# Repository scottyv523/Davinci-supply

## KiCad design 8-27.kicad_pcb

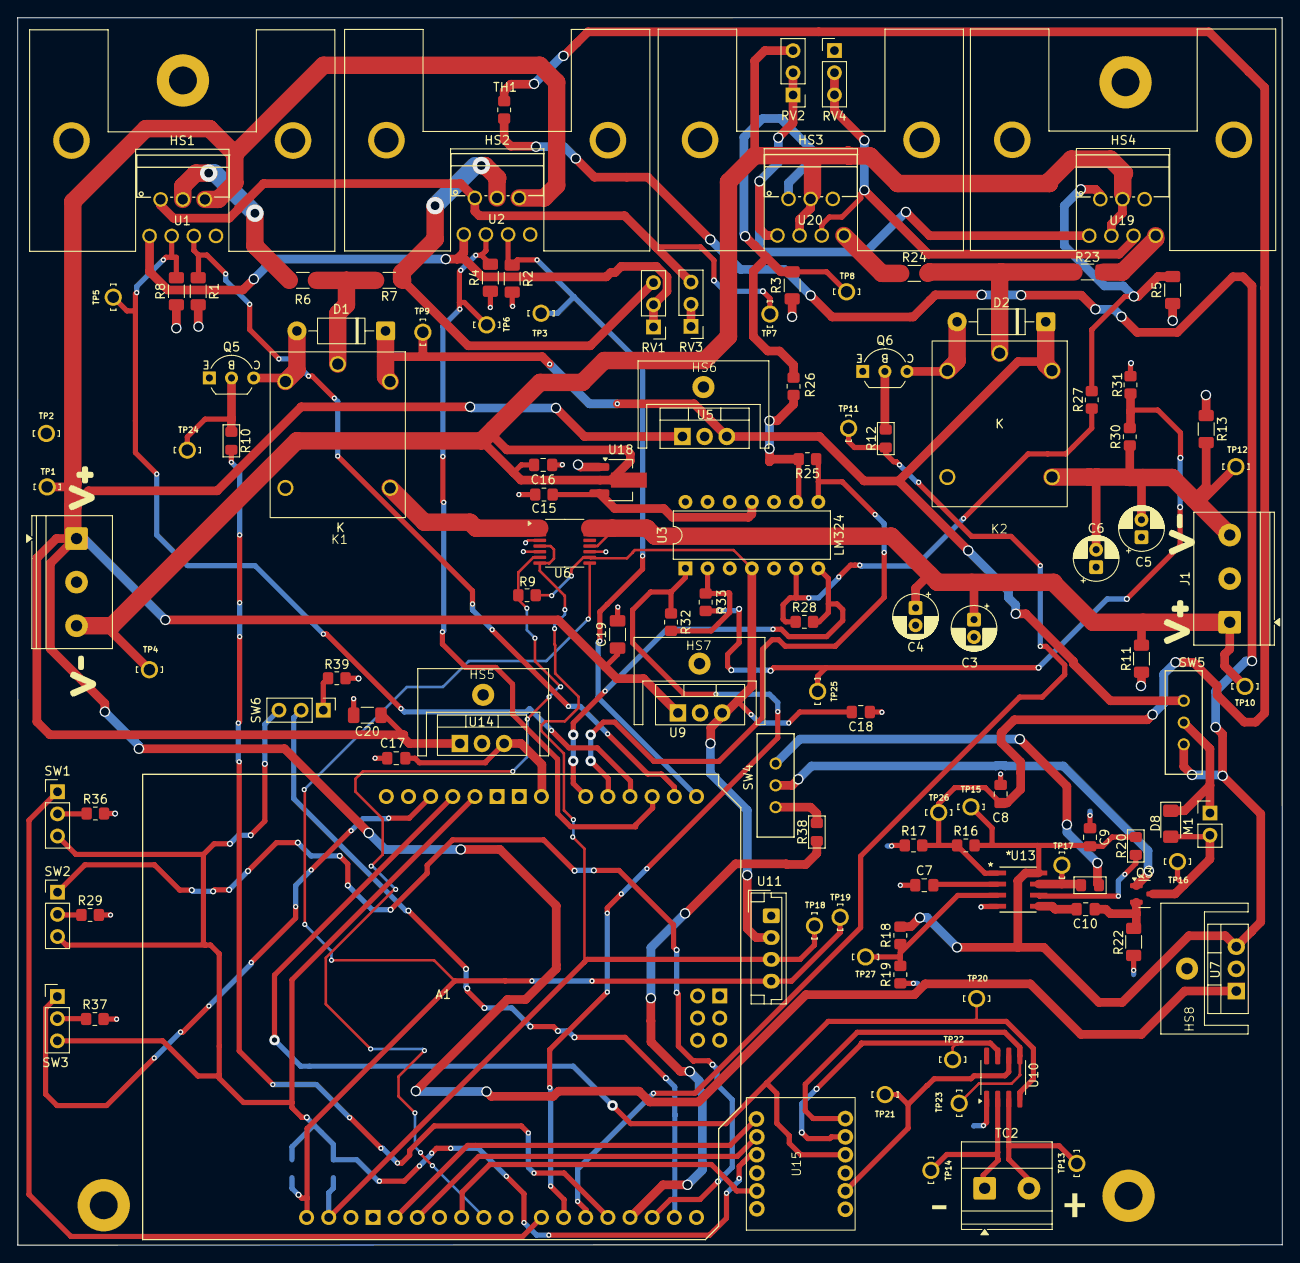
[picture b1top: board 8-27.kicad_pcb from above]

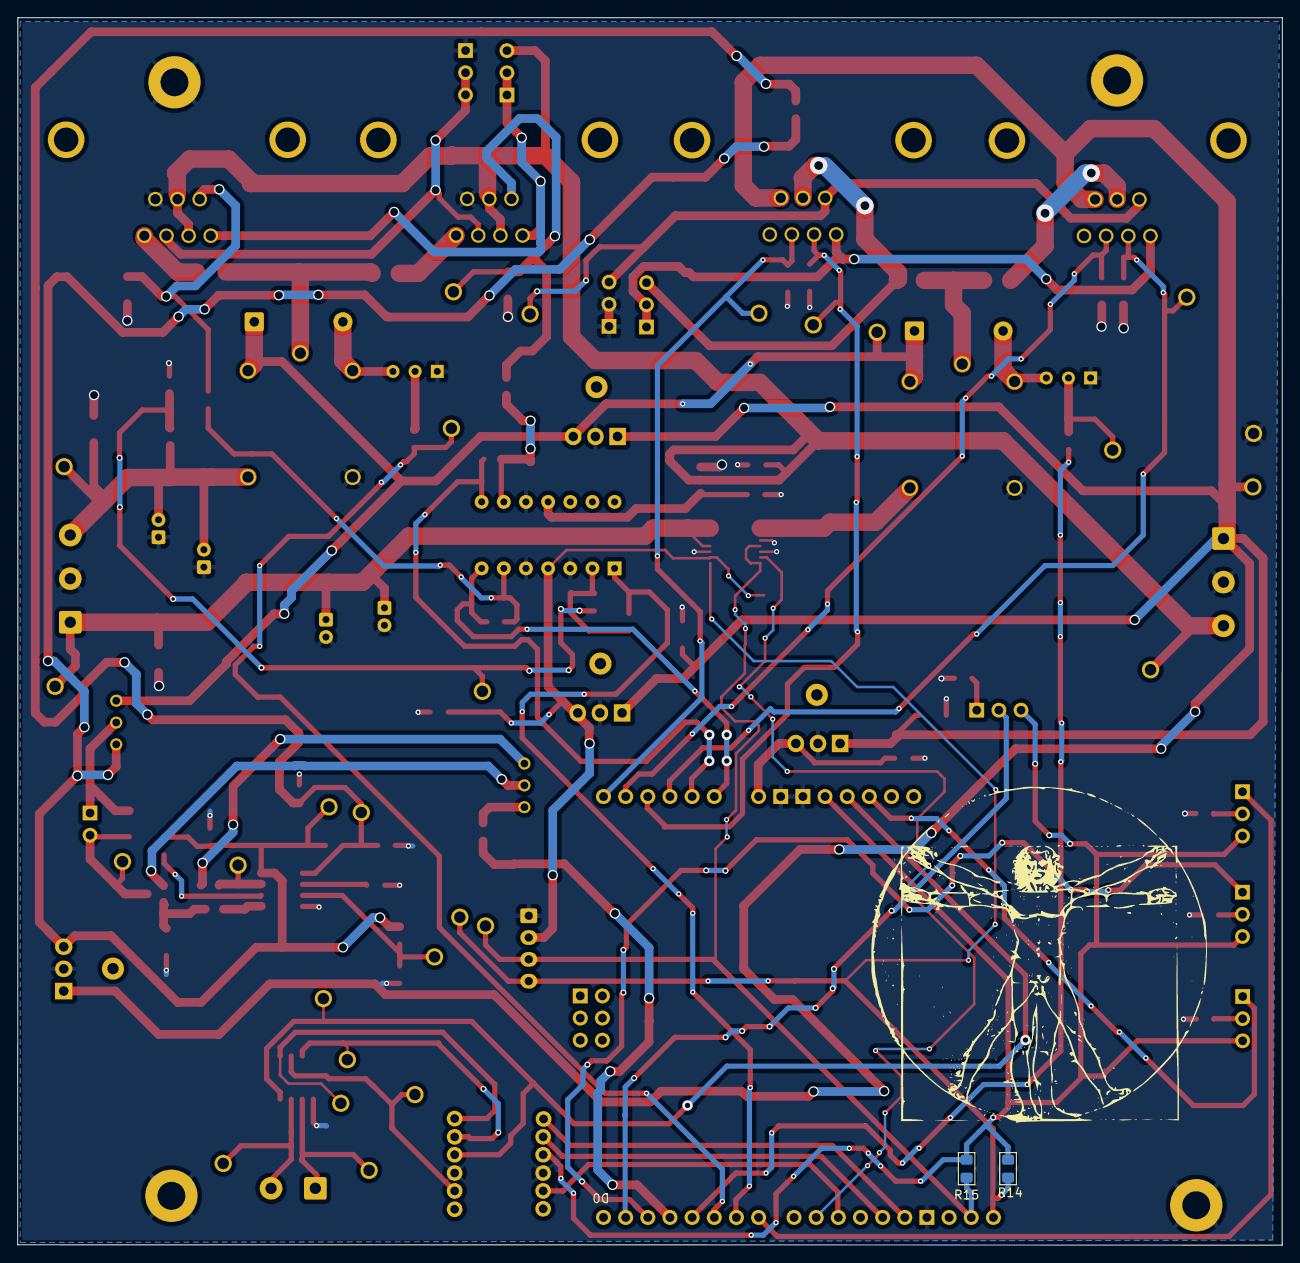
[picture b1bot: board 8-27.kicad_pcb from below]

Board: 2 copper layers, 145.0 x 140.7 mm, 135 parts (7 on the bottom side), 74 nets.

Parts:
A1: Arduino_Leonardo
C3, C4, C5, C6: 10uF; CP_Radial_D5.0mm_P2.00mm
C7, C9: 1uF; C_0805_2012Metric_Pad1.18x1.45mm_HandSolder
C8: .01uF; C_0805_2012Metric_Pad1.18x1.45mm_HandSolder
C10: .1uF; C_0805_2012Metric_Pad1.18x1.45mm_HandSolder
C15: .1uF; R_0805_2012Metric_Pad1.20x1.40mm_HandSolder
C16: .33uF; C_0805_2012Metric_Pad1.18x1.45mm_HandSolder
C17, C18: 1 uF; C_0805_2012Metric_Pad1.18x1.45mm_HandSolder
C19, C20: 33 uF; C_1206_3216Metric_Pad1.33x1.80mm_HandSolder
D1, D2: 1N4007; D_DO-41_SOD81_P10.16mm_Horizontal
D8: D_Schottky_Generic; D_1206_3216Metric_Pad1.42x1.75mm_HandSolder
H1, H2, H3, H4: M3_Hole_With_Spacer_H10mm; MountingHole_3.2mm_With_Spacer_H10mm
HS1, HS2, HS3, HS4: HSE-B250-04H; HSINK_HSE-B250-04H
HS5, HS6, HS7, HS8: Heatsink; Heatsink Amazon
J1: Power Out; TerminalBlock_Phoenix_PT-1,5-3-5.0-H_1x03_P5.00mm_Horizontal
J2: Power In; TerminalBlock_Phoenix_PT-1,5-3-5.0-H_1x03_P5.00mm_Horizontal
K1, K2: Relay_SPDT; JQC-3F(T73)
M1: Fan; PinHeader_1x02_P2.54mm_Vertical
Q3: MMBT2222A; SOT-23
Q5, Q6: 2N2222A-TO92; TO-92_Inline_Wide_EBC
R1, R2: 5k; R_1206_3216Metric_Pad1.30x1.75mm_HandSolder
R3, R4, R5, R8, R11, R13: 10K; R_1206_3216Metric_Pad1.30x1.75mm_HandSolder
R6, R7, R23, R24: 10m; R_1206_3216Metric_Pad1.30x1.75mm_HandSolder
R9: 2K2; R_0805_2012Metric_Pad1.20x1.40mm_HandSolder
R10, R12: 1K; R_0805_2012Metric_Pad1.15x1.40mm_HandSolder
R14, R15, R20: 10K; R_0805_2012Metric_Pad1.15x1.40mm_HandSolder
R16: 237K; R_0805_2012Metric_Pad1.20x1.40mm_HandSolder
R17: 45.3K; R_0805_2012Metric_Pad1.20x1.40mm_HandSolder
R18: 32.4K; R_0805_2012Metric_Pad1.20x1.40mm_HandSolder
R19: 17.8K; R_0805_2012Metric_Pad1.20x1.40mm_HandSolder
R21, R38: 800; R_0805_2012Metric_Pad1.15x1.40mm_HandSolder
R22: 3; R_1206_3216Metric_Pad1.30x1.75mm_HandSolder
R25, R28, R29, R31, R36, R37, R39: 10K; R_0805_2012Metric_Pad1.20x1.40mm_HandSolder
R26, R27: 0R; R_0805_2012Metric_Pad1.20x1.40mm_HandSolder
R30: 50K; R_0805_2012Metric_Pad1.20x1.40mm_HandSolder
R32, R33: 100K; R_0805_2012Metric_Pad1.20x1.40mm_HandSolder
RV1: 200K; PinHeader_1x03_P2.54mm_Vertical
RV2: 50K; PinHeader_1x03_P2.54mm_Vertical
RV3, RV4: 500K; PinHeader_1x03_P2.54mm_Vertical
SW1, SW2, SW3, SW6: SW_MEC_5E; PinHeader_1x03_P2.54mm_Vertical
SW4, SW5: SW_SPDT; SW_1218_SPDT
TC2: Thermocouple_Block; TerminalBlock_Phoenix_MKDS-1,5-2-5.08_1x02_P5.08mm_Horizont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
TH1: Thermistor; R_0805_2012Metric_Pad1.20x1.40mm_HandSolder
TP1, TP2, TP3, TP4, TP5, TP6, TP7, TP8, TP9, TP10, TP11, TP12, TP13, TP14, TP15, TP16, TP17, TP18, TP19, TP20, TP21, TP22, TP23, TP24, TP25, TP26, TP27: TestPoint; KEYSTONE_4952
U1, U2: LT3081xT7; TO220-7_T_LIT
U3: LM324; DIP-14_W7.62mm
U5: LM7812_TO220; TO-220-3_Vertical
U6: INA260; TSSOP-16_4.4x5mm_P0.65mm
U7: LM7805CT; TO-220-3_Vertical
U9: LM7805_TO220; TO-220-3_Vertical
U10: MAX31855KASA; SOIC-8_3.9x4.9mm_P1.27mm
U11: LCD 20x04; JST_EH_B4B-EH-A_1x04_P2.50mm_Vertical
U13: TC647BEOATR; SOIC8-N_MC_MCH
U14: L7808CV; TO-220-3_Vertical
U15: Hiletgo I2C LLC Bi-Directional 3.3-5V; Hiletgo LLC
U18: L7905; SOT-89-3_Handsoldering
U19, U20: LT3091ET7-PBF; TO220-7_T_LIT
kibuzzard-68CB74DE: G***; kibuzzard-68CB74DE
kibuzzard-68CB74F5: G***; kibuzzard-68CB74F5
kibuzzard-68CB749D: G***; kibuzzard-68CB749D
kibuzzard-68CB751C: G***; kibuzzard-68CB751C
kibuzzard-68CB7484: G***; kibuzzard-68CB7484
kibuzzard-68CB7542: G***; kibuzzard-68CB7542

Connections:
+12V: D1.1 (K), D2.1 (K), K1.2 (in), K2.2 (in), SW5.3 (C), TP9.1, U5.3 (VO)
/CLK: A1.28 (D13), U15.7 (HV1)
/Chip Select: A1.25 (D10), U15.11 (HV3)
/Control PCB/3V3: A1.4 (3V3), TP20.1, U10.4 (V_{CC}), U15.3 (LV)
/Control PCB/+5V: C18.2, R9.1, U3.4 (V+), U6.10 (VS), U9.3 (VO), U11.2 (VCC)
/Control PCB/+5V ARD VS: A1.5 (+5V), R14.2, R15.2, SW1.3 (K), SW2.3 (K), SW3.3 (K), SW6.3 (K), U15.9 (HV)
/Control PCB/- Vsense: A1.21 (D6), R32.1, U3.1
/Control PCB/A0 port: A1.9 (A0), R28.2, U3.7
/Control PCB/A1 port: A1.10 (A1), R25.1, U3.8
/Control PCB/A2 port: A1.11 (A2), R8.2, TP5.1, U1.3 (IMON)
/Control PCB/A3 port: A1.12 (A3), R4.2, TP6.1, U2.3 (IMON)
/Control PCB/ARD SCL: A1.32 (SCL/D3), R14.1, TP19.1, U6.9 (SCL), U11.4 (SCL)
/Control PCB/ARD SDA: A1.31 (SDA/D2), R15.1, TP18.1, U6.5 (A0), U6.8 (SDA), U11.3 (SDA)
/Control PCB/D3 PWM: A1.18 (D3/SCL), R38.1
/Control PCB/D4 I/O: A1.19 (D4), R10.2
/Control PCB/D5 I/O: A1.20 (D5), R12.1, TP11.1
/Control PCB/INA Alert: A1.24 (D9), R9.2, U6.7 (ALERT)
/Data: A1.27 (D12), U15.8 (HV2)
/LT3081_3091 REGULATOR PCB/-V ADJ Out: C5.2, C6.2, J1.3, K2.4 (NC), R13.2, R30.2, TP12.1
/LT3081_3091 REGULATOR PCB/I LIM/ADJ: RV1.1, RV1.2, U1.1 (ILIM), U2.1 (ILIM)
/LT3081_3091 REGULATOR PCB/Temp 1: A1.13 (A4), R1.1, U1.5 (TEMP)
/LT3081_3091 REGULATOR PCB/Temp 2: A1.14 (A5), R2.1, TP3.1, U2.5 (TEMP)
/LT3081_3091 REGULATOR PCB/V Set: RV3.3, TP7.1, U1.2 (SET), U2.2 (SET)
/LT3081_3091 REGULATOR PCB/V+ ADJ Out: C3.1, C4.1, J1.1, R11.1, TP10.1, U6.12 (VBUS), U6.14 (IN-), U6.15 (IN-), U6.16 (IN-)
/LT3081_3091 REGULATOR PCB/V+ PRE-REG: C19.1, C20.1, J2.1, TP1.1, U1.6 (IN), U2.6 (IN), U5.1 (VI), U7.1 (IN), U9.1 (VI), U14.1 (IN)
/LT3081_3091 REGULATOR PCB/V- ADJ Out: K2.1 (COM), R23.2, R24.2
/LT3081_3091 REGULATOR PCB/V- PRE-REG: C16.2 (-), J2.3, RV2.3, TP4.1, U18.2 (VI), U19.3 (*SHDN), U19.4 (IN), U20.3 (*SHDN), U20.4 (IN)
GND: A1.6 (GND), A1.7 (GND), A1.29 (GND), C3.2, C4.2, C5.1, C6.1, C7.1, C8.2, C9.1, C15.1 (+), C16.1 (+), C17.1, C18.1, C19.2, C20.2, H1.1, H2.1, H3.1, H4.1, J1.2, J2.2, K1.5 (NO), K2.5 (NO), Q5.1 (E), Q6.1 (E), R1.2, R2.2, R3.1, R4.1, R5.1, R8.1, R11.2, R13.1, R17.1, R19.1, R22.2, R29.2, R31.1, R36.2, R37.2, R39.1, RV3.1, RV3.2, RV4.1, TP2.1, U3.3 (+), U3.5 (+), U3.10 (+), U5.2 (GND), U6.4 (A1), U6.6 (GND), U6.11 (GND), U7.2, U9.2 (GND), U10.1 (GND), U11.1 (GND), U13.4 (GND), U14.2, U15.4 (GND), U15.10 (GND), U18.1 (GND), U19.6 (GND), U20.6 (GND)
unnamed: A1.16 (D1/TX), SW6.2
unnamed: A1.17 (D2/SDA), SW2.1
unnamed: A1.22 (D7), SW1.1
unnamed: A1.8 (VIN), C17.2, U14.3 (OUT)
unnamed: A1.3 (~RESET), SW3.1
unnamed: C15.2 (-), U3.11 (V-), U18.3 (VO)
unnamed: D1.2 (A), K1.3 (out), Q5.3 (C)
unnamed: D2.2 (A), K2.3 (out), Q6.3 (C)
unnamed: D8.2 (A), M1.2 (-), Q3.3 (C), TP16.1
unnamed: D8.1 (K), M1.1 (+), SW5.2 (B)
unnamed: K1.1 (COM), R6.2, R7.2
unnamed: K1.4 (NC), U6.1 (IN+), U6.2 (IN+), U6.3 (IN+)
unnamed: Q3.1 (B), SW4.2 (B)
unnamed: C10.2, Q3.2 (E), R22.1
unnamed: Q5.2 (B), R10.1, TP24.1
unnamed: Q6.2 (B), R12.2
unnamed: R29.1, SW2.2
unnamed: R30.1, R31.2, R33.2, TP25.1
unnamed: R36.1, SW1.2
unnamed: R37.1, SW3.2
unnamed: R39.2, SW6.1
unnamed: R21.2, SW4.1 (A)
unnamed: R38.2, SW4.3 (C)
unnamed: C9.2, R16.2, R18.2, R20.2, SW5.1 (A), TH1.1, TP15.1, U7.3 (OUT), U13.8 (VDD)
unnamed: TC2.2 (+), TP13.1, U10.3 (T+)
unnamed: TC2.1 (-), TP14.1, U10.2 (T-)
unnamed: R6.1, U1.4 (OUT)
unnamed: R7.1, RV1.3, U2.4 (OUT)
unnamed: R32.2, R33.1, U3.2 (-)
unnamed: R27.2, R28.1, U3.6 (-)
unnamed: R25.2, R26.2, U3.9 (-)
unnamed: TP23.1, U10.5 (SCK), U15.1 (LV1)
unnamed: TP22.1, U10.7 (SO), U15.2 (LV2)
unnamed: TP21.1, U10.6 (~CS), U15.5 (LV3)
unnamed: C7.2, U13.2 (CF)
unnamed: R20.1, U13.6 (FAULT)
unnamed: C10.1, U13.5 (SENSE)
unnamed: R21.1, TP17.1, U13.7 (VOUT)
unnamed: C8.1, R16.1, R17.2, TH1.2, TP26.1, U13.1 (Vin)
unnamed: R18.1, R19.2, TP27.1, U13.3 (Vmin)
unnamed: RV2.1, RV2.2, U19.1 (ILIM), U20.1 (ILIM)
unnamed: R5.2, R27.1, U19.2 (IMONN)
unnamed: R23.1, U19.7 (OUT)
unnamed: RV4.2, RV4.3, U19.5 (SET), U20.5 (SET)
unnamed: R3.2, R26.1, TP8.1, U20.2 (IMONN)
unnamed: R24.1, U20.7 (OUT)
